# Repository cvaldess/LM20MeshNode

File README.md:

# LM20MeshNode

Pocket [Meshtastic](https://meshtastic.org/) node built around the Nordic **nRF54LM20A**
(Minew ME54BS13 module), with an Ebyte **E22-900MM22S** (SX1262) LoRa module, an Ebyte
**E108-GN04S** GNSS receiver and a Nordic **nPM1300** PMIC for a single-cell LiPo battery.
It connects to the phone over Bluetooth LE.

| Front | Back |
|-------|------|
|  |  |

> **Status:** revision 0.1, not yet manufactured or tested. A Meshtastic firmware variant is
> under review as a draft, not yet tested on hardware: see [Meshtastic firmware](#meshtastic-firmware).

## Features

- **MCU:** Minew ME54BS13 (nRF54LM20A, Bluetooth LE with integrated antenna), USB-C to the
  nRF54LM20A USB port, 2×5 1.27 mm Cortex Debug (SWD) header (J201) and debug UART pads.
- **LoRa:** Ebyte E22-900MM22S (SX1262, up to 22 dBm) with U.FL antenna connector (J301).
  TXEN is driven by DIO2 on the board; RXEN comes from the MCU.
- **GNSS:** Ebyte E108-GN04S with U.FL antenna connector (J401). Fit L401 (82 nH) to power an
  active antenna. The GNSS supply (nPM1300 BUCK1) is off at power-up and is switched by
  firmware; the backup supply (V_BCKP) stays on from 3.3 V.
- **Power:** nPM1300 PMIC with USB-C input and ESD protection, 1S LiPo charger (JST PH 2.0,
  J102), on-board 10 kΩ NTC, 3.3 V main rail (BUCK2), power button (SW101) on SHPHLD, charge
  and error LEDs, and a battery voltage divider to an ADC input.
- **User interface:** 0.91" 128×32 OLED (SSD1306) on the back, three side buttons (UP, OK,
  DOWN), magnetic buzzer and a status LED.
- **Sensors:** Nyfea SHT41-P-NF temperature/humidity sensor (SHT41 compatible), thermally
  isolated by a slot, and an ST LSM6DS3TR-C IMU wired for wake-on-motion (INT1 on P0.02).
- **Expansion:** 4-pin 1 mm I²C connector (J501, Qwiic-style pinout: GND, 3.3 V, SDA, SCL).
- **Board:** 4 layers (signal / GND / 3.3 V / signal), 40 × 85.68 mm, 1.6 mm, M2 mounting
  holes. All SMD parts are on the top side.

## nRF54LM20A pin map

| Function | Pin | Notes |
|----------|-----|-------|
| LoRa SPI (SPIM22): SCK, MOSI, MISO, NSS | P1.17, P1.16, P1.15, P1.18 | |
| LoRa BUSY, DIO1, NRST | P1.19, P1.23, P1.26 | |
| LoRa RXEN | P1.13 | TXEN from DIO2; optional MCU TXEN on P1.12 (R302, not fitted) |
| I²C (TWIM30): SDA, SCL | P0.03, P0.04 | 4.7 kΩ pull-ups |
| GNSS UART (UARTE20): MCU TX → GNSS RXD, GNSS TXD → MCU RX | P1.03, P1.29 | 1 kΩ series resistors |
| GNSS PPS, reset | P1.04, P1.00 | |
| GNSS power enable | P1.05 | To nPM1300 GPIO0 |
| PMIC interrupt | P1.06 | From nPM1300 GPIO1 |
| Battery voltage (divider 2 × 1 MΩ) | P1.30 (AIN2) | |
| Buttons UP, OK, DOWN | P1.27, P1.28, P1.25 | |
| Buzzer (PWM) | P1.09 | |
| Status LED | P2.00 | |
| IMU INT1, INT2 | P0.02, P0.05 | P0 can wake the chip from System OFF |
| Debug UART (UARTE00): TX, RX | P2.02, P2.07 | Test pads |

I²C devices: nPM1300 `0x6B`, LSM6DS3TR-C `0x6A`, SHT41 `0x44`, OLED `0x3C`.

### Firmware notes

- The nPM1300 starts with the **battery charger disabled**. Firmware must enable charging
  over I²C. The board is designed so that LoRa and Bluetooth work without a PMIC driver.
- The E22-900MM22S used here has a crystal, not a TCXO: do not define a DIO3 TCXO voltage.
- The GNSS rail (BUCK1) must be set to 3.3 V and enabled by firmware.

## Meshtastic firmware

The `lm20meshnode` variant is under review upstream. All three pull requests are open, and
nothing has run on hardware yet:

| Part | Pull request |
|------|--------------|
| Meshtastic variant (draft, on top of the nRF54LM20-DK support in [#12130](https://github.com/meshtastic/firmware/pull/12130)) | [meshtastic/firmware#12354](https://github.com/meshtastic/firmware/pull/12354) |
| Arduino core variant | [andyshinn/nRF54_Arduino#3](https://github.com/andyshinn/nRF54_Arduino/pull/3) |
| Bootloader board | [andyshinn/nRF54_Bootloader#3](https://github.com/andyshinn/nRF54_Bootloader/pull/3) |

Until they are merged, the variant builds from the `feat/lm20meshnode-variant` branch of
[cvaldess/firmware](https://github.com/cvaldess/firmware/tree/feat/lm20meshnode-variant) with
`pio run -e lm20meshnode`. The core and the bootloader come from forks (the core at a pinned commit,
the bootloader at the tag `v0.5.0-lm20meshnode.1`).

What the variant does on this board:

- **nPM1300**, set up over I²C at boot: BUCK1 (GNSS rail) at 3.3 V, switched by the PMIC's GPIO0,
  which the GPS code drives from P1.05; battery charger on at 200 mA (`NPM1300_CHARGE_CURRENT_MA`),
  4.20 V (4.00 V in the warm region), with the on-board 10 kΩ NTC; USB input limit 500 mA. BUCK2,
  the 3.3 V main rail, is left on its VSET2 setting. After USB is unplugged and plugged in again,
  the PMIC goes back to its 100 mA startup input limit until the next boot.
- **LoRa** with RXEN from the MCU and TXEN from DIO2, no TCXO. **GNSS** on `Serial1` at 38400 bps.
- **Buttons:** UP, DOWN and OK navigate the screen (up/down input driver). **OLED** at 128×32,
  **buzzer**, **status LED**, **battery** level from AIN2, and the SHT41 and LSM6DS3TR-C drivers.
- **USB-C:** console and Meshtastic API over USB CDC; firmware updates over USB (serial DFU or a
  UF2 drive) or over Bluetooth.
- **Bootloader** (64 KB, application at `0x10000`): hold **OK** at reset for USB DFU (UF2 drive
  `LM20MN-BOOT`), **OK + DOWN** for Bluetooth OTA. The status LED shows the bootloader state.

Not tested yet, besides the board itself: the nPM1300 setup, GPS on the nRF54 platform (no other
nRF54 variant uses it so far), the 128×32 screen layout and the battery reading through the
2 × 1 MΩ divider.

## Manufacturing

The [`fab/pcbway/`](fab/pcbway/) folder contains:

- `nrflm20-meshnode_rev0.1_pcbway.zip`: Gerber files (4 copper layers, masks, top paste,
  silkscreen, outline), Excellon drill files (PTH and NPTH) and an IPC-D-356 netlist.
- `gerber/`: the same files unzipped, plus drill maps and the drill report.
- `nrflm20-meshnode-BOM-PCBWay.csv`: bill of materials (40 lines, 71 parts) with manufacturer part
  numbers and LCSC codes. A few passives are generic parts, listed by specification.
- `nrflm20-meshnode-CPL-PCBWay.csv`: component placement (centroid) file in millimetres, in the
  same coordinate system as the Gerber files. The OLED (DS501) is the only part on the bottom side.
- `pedido_pcbway.txt`: order settings and pre-production checks (in Spanish).

Not fitted (DNP) and left out of the BOM and placement files: R302, R404, C303, C304. Mounting
holes and test points are not parts and are left out too.

Board: 4 layers, 1.6 mm, 1 oz copper, ENIG recommended, minimum track/space 0.2 mm, minimum
drill 0.3 mm. Stencil: top side only, 0.10 mm. The standard PCBWay 4-layer stackup is fine;
impedance control is not needed.

The files are generated from the saved board with `docs/gen/fab_pcbway.py` (Gerber, drill,
IPC-D-356) and `docs/gen/bom_cpl_pcbway.py` (BOM and placement), using KiCad's Python.

## Design files

- [KiCad 10](https://www.kicad.org/) project: `nrflm20-meshnode.kicad_pro`. The root schematic
  has five sheets: power, MCU, LoRa, GNSS and interface.
- `libs/`: project symbols, footprints and 3D models. The ME54BS13 and E108-GN04S 3D models
  were drawn from their datasheets (generators in `docs/gen/`).
- `docs/`: block diagram and schematic drafts (SVG). `docs/gen/` has the Python scripts used
  during the design.
- `lista_compra.txt`: shopping list (in Spanish).

Some footprints and 3D models come from [easyeda2kicad](https://github.com/uPesy/easyeda2kicad.py)
(`${EASYEDA2KICAD}`). The footprints are stored in the board file, but their 3D models are
not included in this repository.

## Credits

- **Designed by:** solutions@cvaldess.com
- **Made with:** [Claude Code](https://claude.com/claude-code), [KiCad](https://www.kicad.org/)
  and [Konnect-EDA](https://github.com/Orchis-ai-LLC/Konnect-EDA)
- **Sponsor:** [PCBWay](https://www.pcbway.com/)

## License

Copyright © 2026 CValdesS.

This source describes Open Hardware and is licensed under the CERN-OHL-S v2
([LICENSE](LICENSE)). You may redistribute and modify this source and make products using it
under the terms of the CERN-OHL-S v2. This source is distributed WITHOUT ANY EXPRESS OR IMPLIED
WARRANTY, INCLUDING OF MERCHANTABILITY, SATISFACTORY QUALITY AND FITNESS FOR A PARTICULAR
PURPOSE. Please see the CERN-OHL-S v2 for applicable conditions.

Source location: https://github.com/cvaldess/LM20MeshNode

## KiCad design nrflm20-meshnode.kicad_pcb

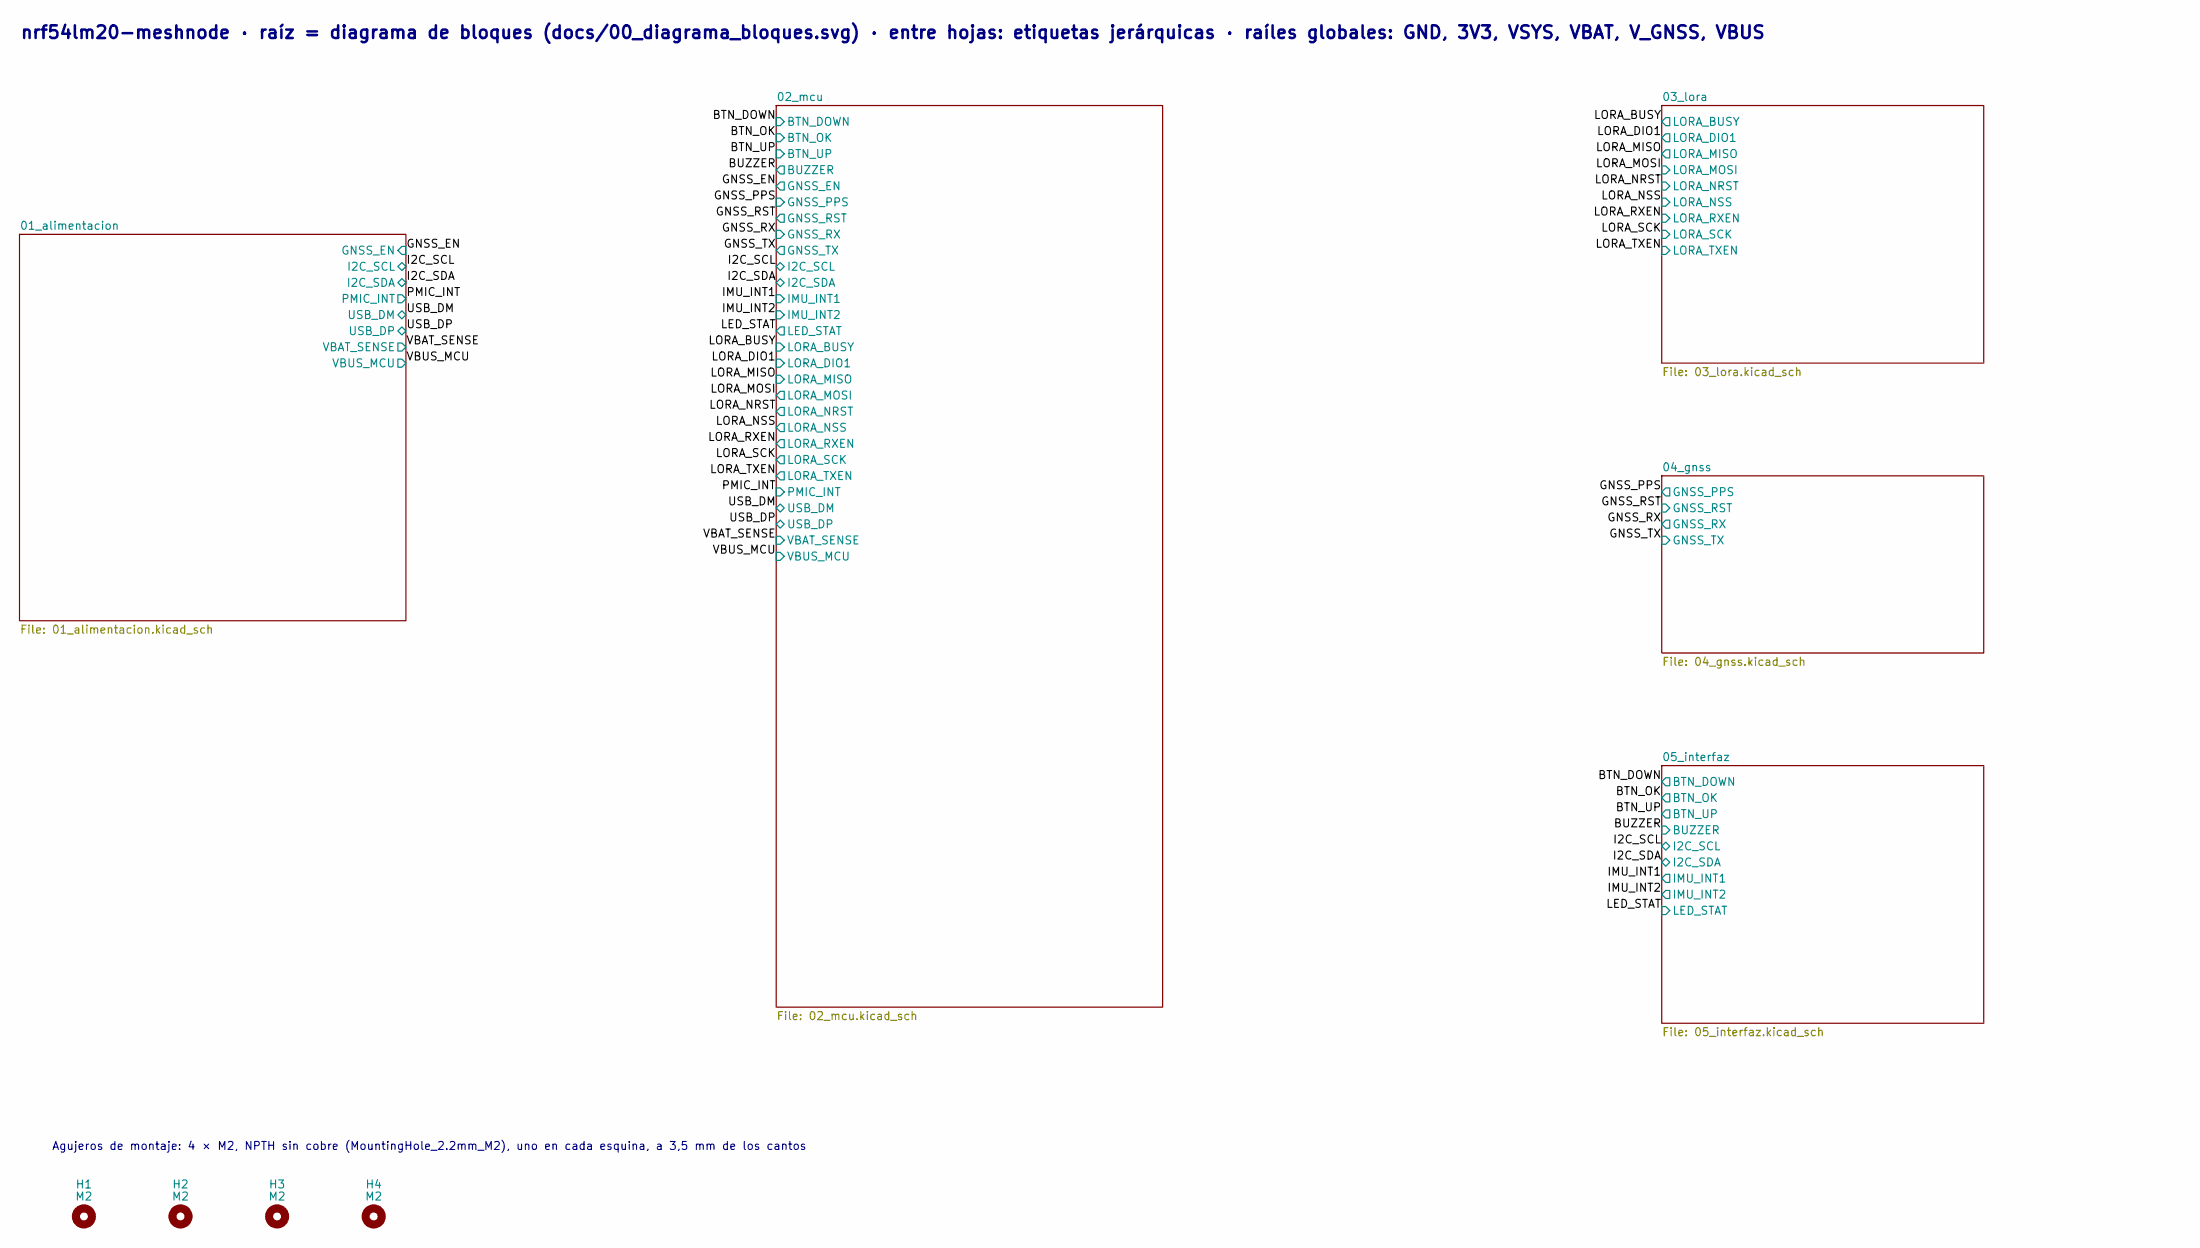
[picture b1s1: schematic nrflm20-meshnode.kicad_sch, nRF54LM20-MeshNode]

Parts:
H1, H2, H3, H4: M2; MountingHole_2.2mm_M2

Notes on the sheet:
nrf54lm20-meshnode · raíz = diagrama de bloques (docs/00_diagrama_bloques.svg) · entre hojas: etiquetas jerárquicas · raíles globales: GND, 3V3, VSYS, VBAT, V_GNSS, VBUS
Agujeros de montaje: 4 × M2, NPTH sin cobre (MountingHole_2.2mm_M2), uno en cada esquina, a 3,5 mm de los cantos

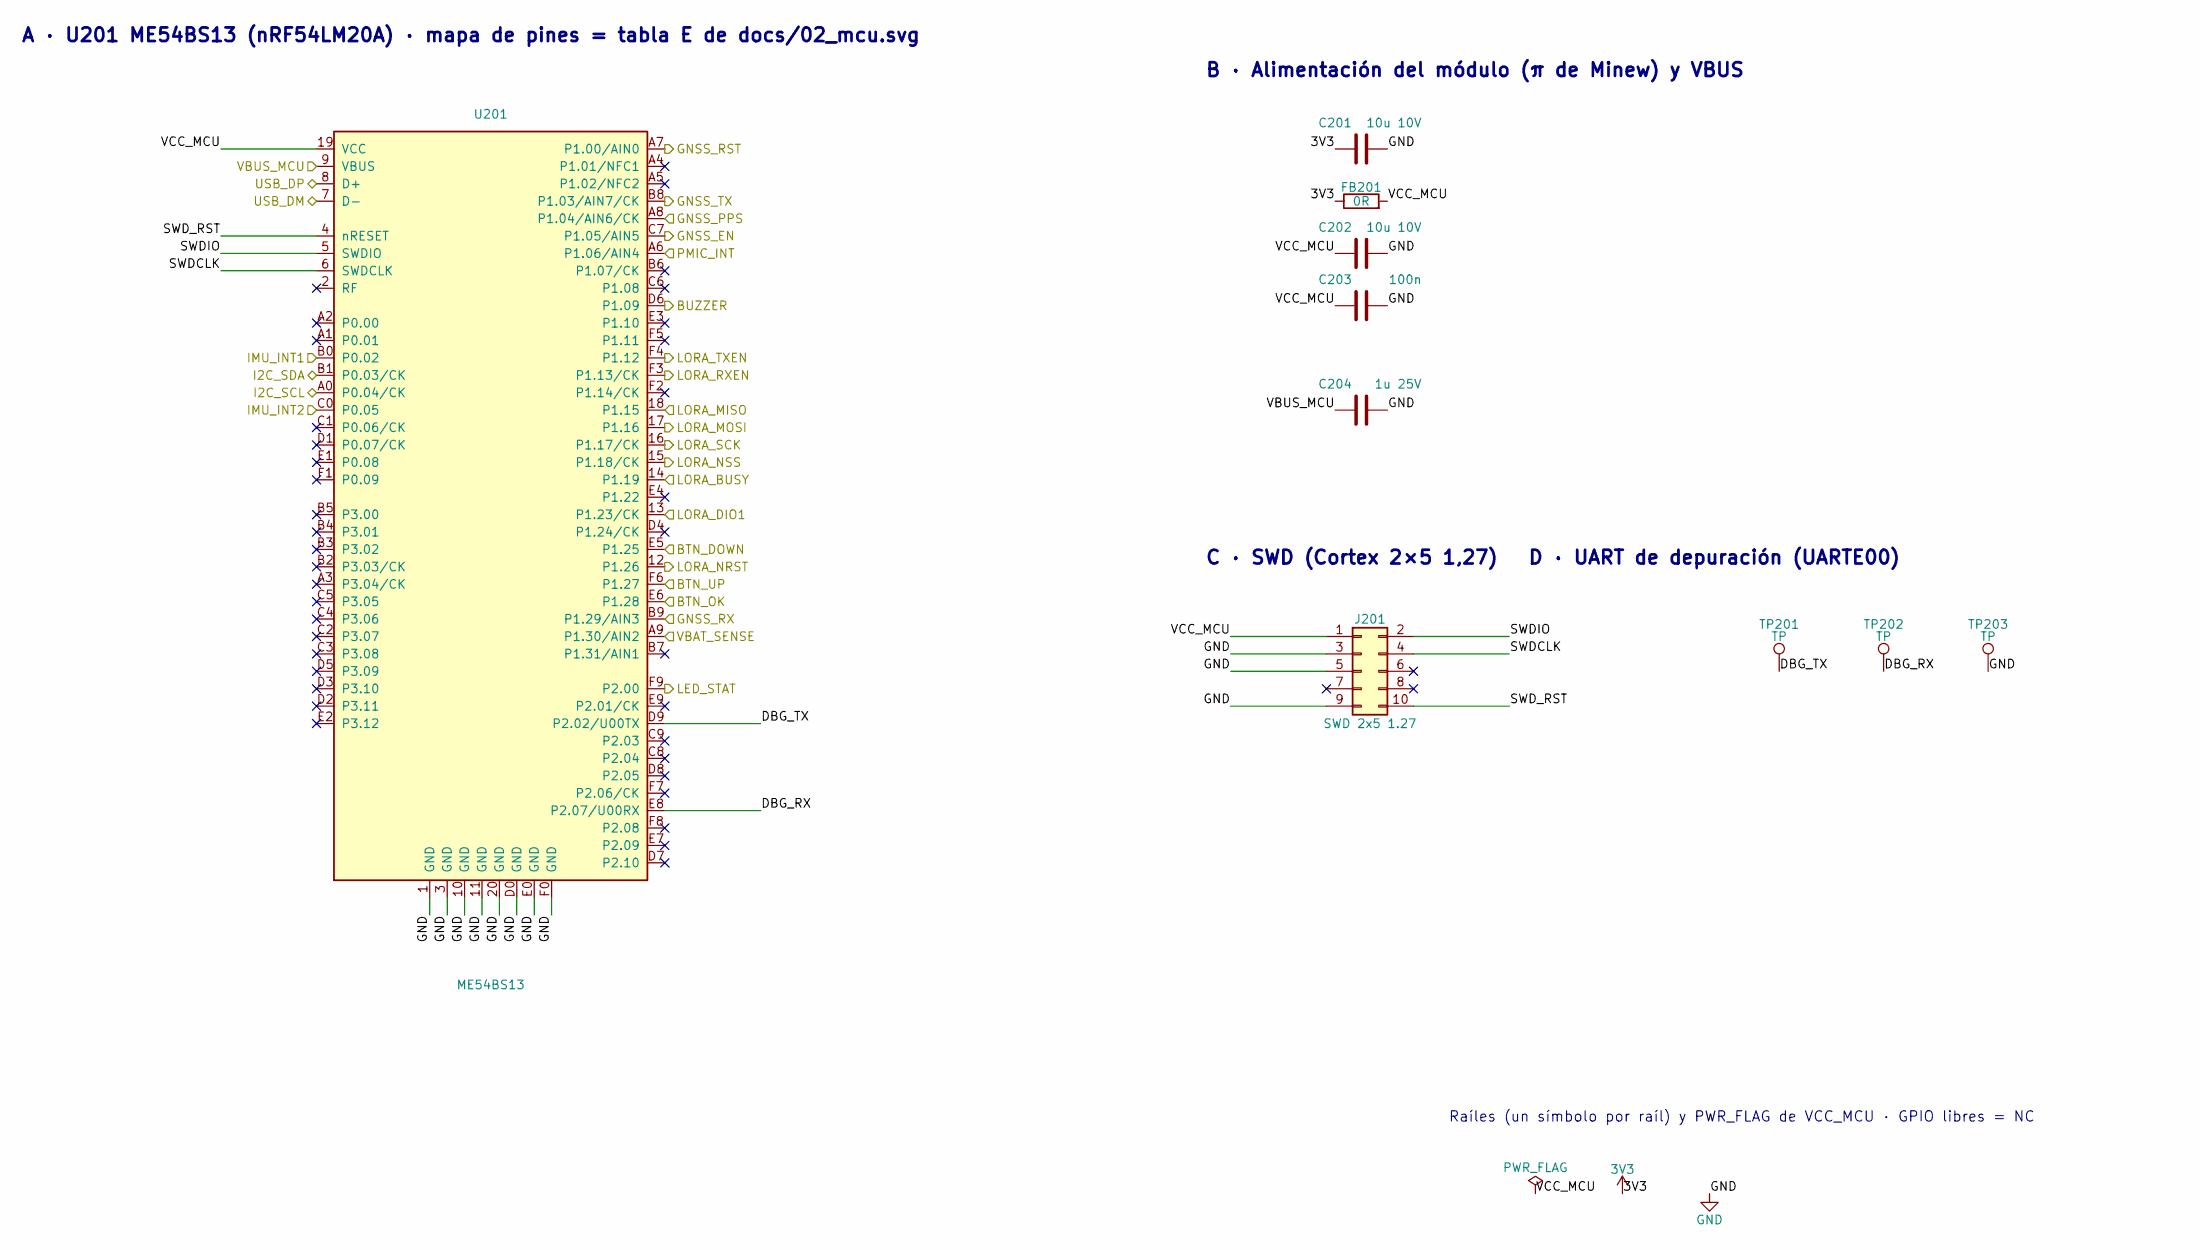
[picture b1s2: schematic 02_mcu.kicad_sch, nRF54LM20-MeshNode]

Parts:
C201, C202: 10u 10V; C_0603_1608Metric
C203: 100n; C_0402_1005Metric; MPN CL05B104KO5NNNC; LCSC Part C1525
C204: 1u 25V; C_0402_1005Metric; MPN CL05A105KA5NQNC; LCSC Part C52923
FB201: 0R; R_0603_1608Metric
J201: SWD 2x5 1.27; PinHeader_2x05_P1.27mm_Vertical_SMD; MPN HX PZ1.27-2x5P TP; LCSC Part C41376037
TP201, TP202, TP203: TP; TestPoint_Pad_D1.0mm
U201: ME54BS13; MPN ME54BS13 (nRF54LM20A)

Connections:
3V3: C201.1, FB201.1; also elsewhere on the board
/02_mcu/DBG_RX: TP202.1 (1_1), U201.E8 (P2.07/U00RX)
/02_mcu/DBG_TX: TP201.1 (1_1), U201.D9 (P2.02/U00TX)
/02_mcu/SWDCLK: J201.4, U201.6 (SWDCLK)
/02_mcu/SWDIO: J201.2, U201.5 (SWDIO)
/02_mcu/SWD_RST: J201.10, U201.4 (nRESET)
/02_mcu/VCC_MCU: C202.1, C203.1, FB201.2, J201.1, U201.19 (VCC)
/BTN_DOWN: U201.E5 (P1.25); also elsewhere on the board
/BTN_OK: U201.E6 (P1.28); also elsewhere on the board
/BTN_UP: U201.F6 (P1.27); also elsewhere on the board
/BUZZER: U201.D6 (P1.09); also elsewhere on the board
/GNSS_EN: U201.C7 (P1.05/AIN5); also elsewhere on the board
/GNSS_PPS: U201.A8 (P1.04/AIN6/CK); also elsewhere on the board
/GNSS_RST: U201.A7 (P1.00/AIN0); also elsewhere on the board
/GNSS_RX: U201.B9 (P1.29/AIN3); also elsewhere on the board
/GNSS_TX: U201.B8 (P1.03/AIN7/CK); also elsewhere on the board
/I2C_SCL: U201.A0 (P0.04/CK); also elsewhere on the board
/I2C_SDA: U201.B1 (P0.03/CK); also elsewhere on the board
/IMU_INT1: U201.B0 (P0.02); also elsewhere on the board
/IMU_INT2: U201.C0 (P0.05); also elsewhere on the board
/LED_STAT: U201.F9 (P2.00); also elsewhere on the board
/LORA_BUSY: U201.14 (P1.19); also elsewhere on the board
/LORA_DIO1: U201.13 (P1.23/CK); also elsewhere on the board
/LORA_MISO: U201.18 (P1.15); also elsewhere on the board
/LORA_MOSI: U201.17 (P1.16); also elsewhere on the board
/LORA_NRST: U201.12 (P1.26); also elsewhere on the board
/LORA_NSS: U201.15 (P1.18/CK); also elsewhere on the board
/LORA_RXEN: U201.F3 (P1.13/CK); also elsewhere on the board
/LORA_SCK: U201.16 (P1.17/CK); also elsewhere on the board
/LORA_TXEN: U201.F4 (P1.12); also elsewhere on the board
/PMIC_INT: U201.A6 (P1.06/AIN4); also elsewhere on the board
/USB_DM: U201.7 (D-); also elsewhere on the board
/USB_DP: U201.8 (D+); also elsewhere on the board
/VBAT_SENSE: U201.A9 (P1.30/AIN2); also elsewhere on the board
/VBUS_MCU: C204.1, U201.9 (VBUS); also elsewhere on the board
GND: C201.2, C202.2, C203.2, C204.2, J201.3, J201.5, J201.9, TP203.1 (1_1), U201.1 (GND), U201.3 (GND), U201.10 (GND), U201.11 (GND), U201.20 (GND), U201.D0 (GND), U201.E0 (GND), U201.F0 (GND); also elsewhere on the board

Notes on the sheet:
B · Alimentación del módulo (π de Minew) y VBUS
A · U201 ME54BS13 (nRF54LM20A) · mapa de pines = tabla E de docs/02_mcu.svg
C · SWD (Cortex 2×5 1,27) D · UART de depuración (UARTE00)
Raíles (un símbolo por raíl) y PWR_FLAG de VCC_MCU · GPIO libres = NC

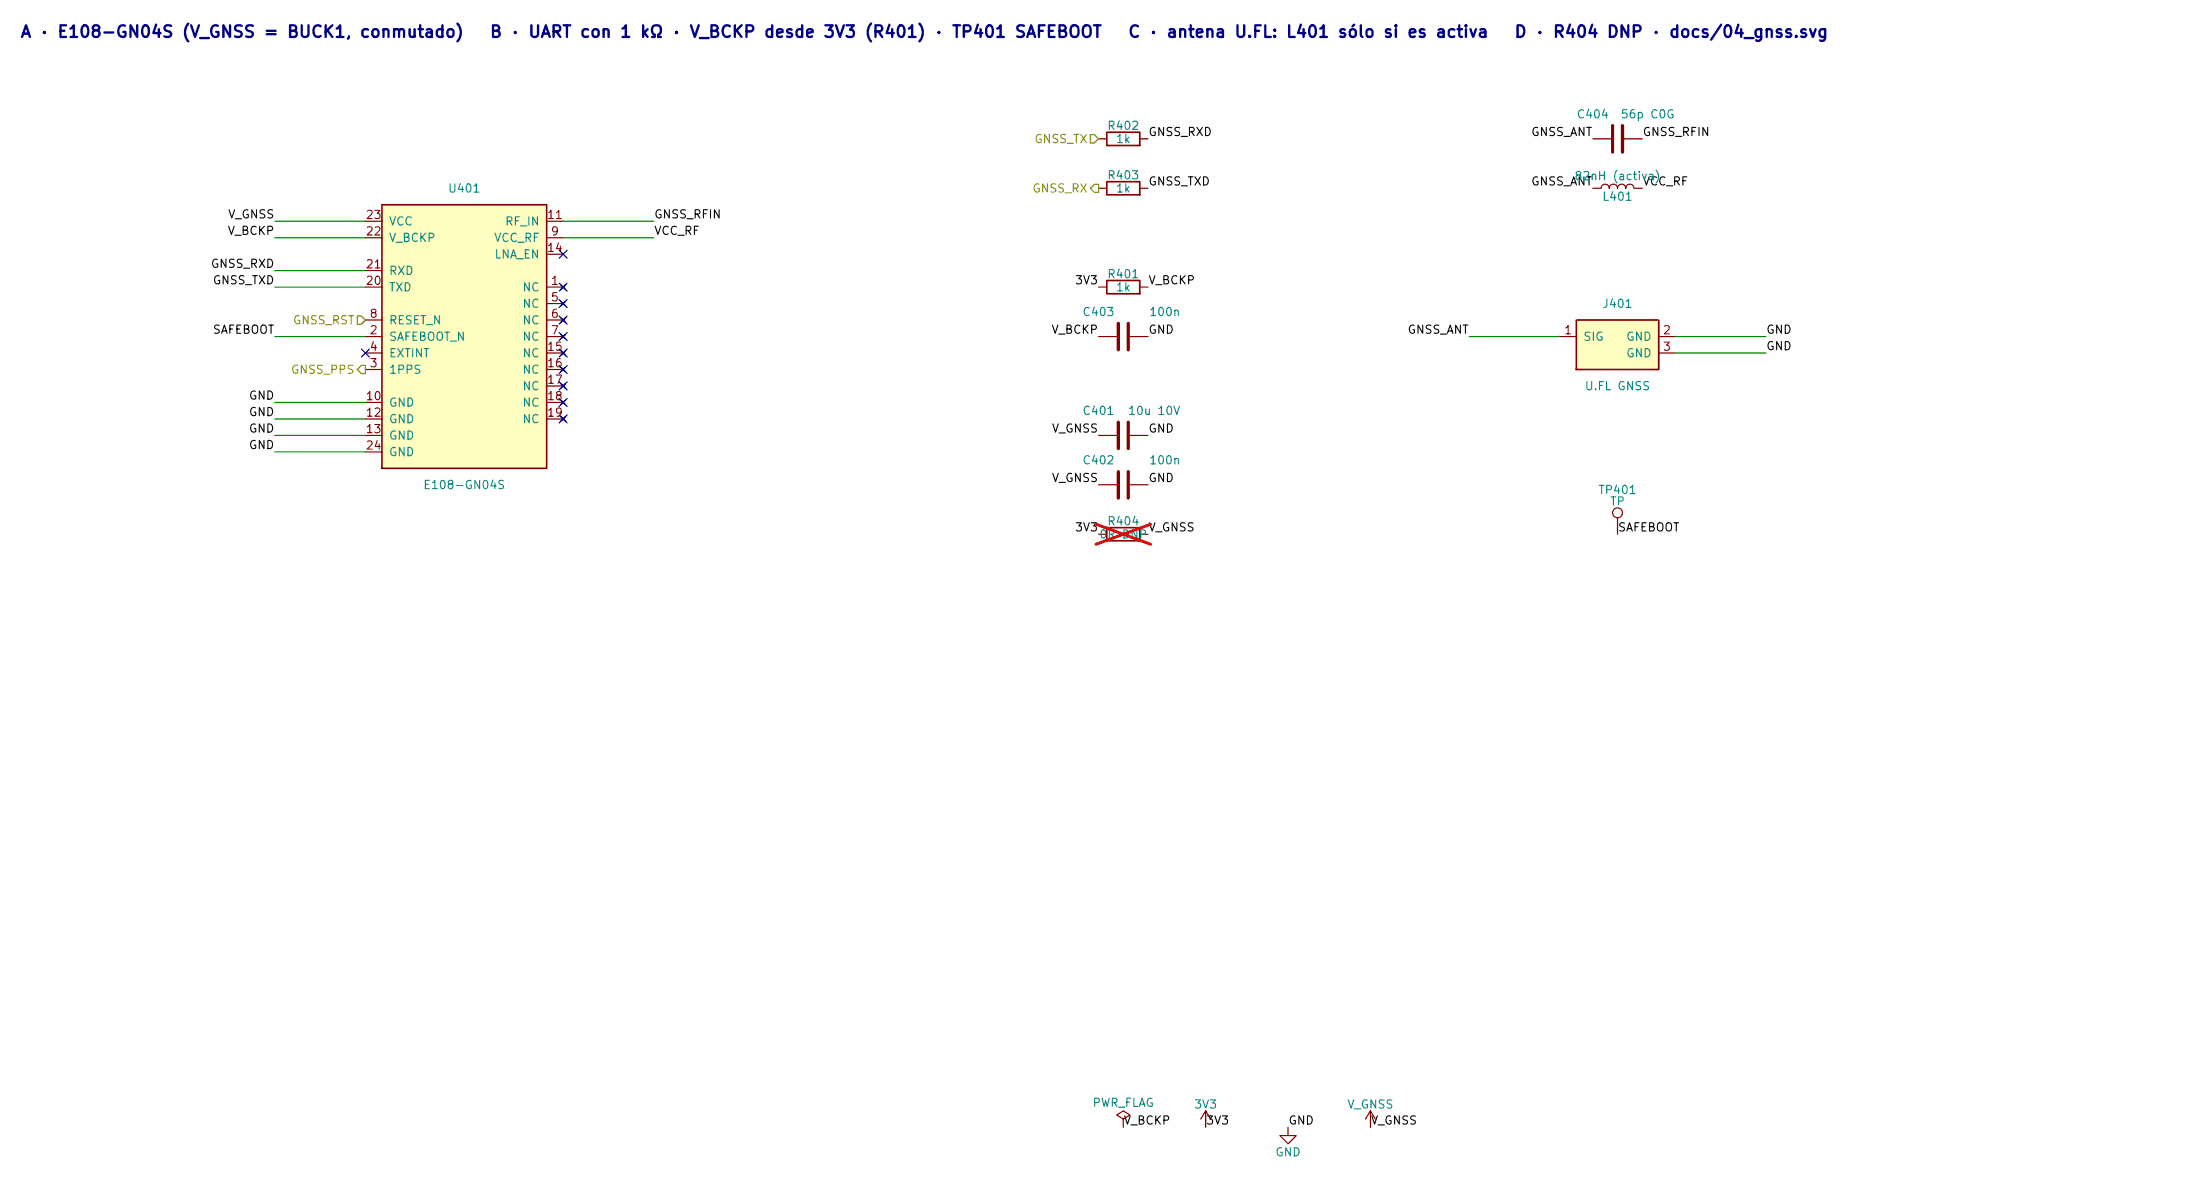
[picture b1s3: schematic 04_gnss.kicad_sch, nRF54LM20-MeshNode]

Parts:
C401: 10u 10V; C_0603_1608Metric
C402, C403: 100n; C_0402_1005Metric; MPN CL05B104KO5NNNC; LCSC Part C1525
C404: 56p C0G; C_0402_1005Metric; MPN CL05C560JB5NNNC; LCSC Part C84707
J401: U.FL GNSS; IPEX-SMD_BWIPX-1-001E; MPN BWU.FL-IPEX1; LCSC Part C5137195
L401: 82nH (activa); L_0402_1005Metric; MPN LQG15HS82NJ02D; LCSC Part C98002
R401, R402, R403: 1k; R_0402_1005Metric; MPN 0402WGF1001TCE; LCSC Part C11702
R404: 0R DNP; R_0402_1005Metric; MPN RC0402FR-070RL; LCSC Part C106231; not fitted
TP401: TP; TestPoint_Pad_D1.0mm
U401: E108-GN04S; MPN E108-GN04S

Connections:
3V3: R401.1, R404.1; also elsewhere on the board
/04_gnss/GNSS_ANT: C404.1, J401.1 (SIG), L401.1
/04_gnss/GNSS_RFIN: C404.2, U401.11 (RF_IN)
/04_gnss/GNSS_RXD: R402.2, U401.21 (RXD)
/04_gnss/GNSS_TXD: R403.2, U401.20 (TXD)
/04_gnss/SAFEBOOT: TP401.1 (1_1), U401.2 (SAFEBOOT_N)
/04_gnss/VCC_RF: L401.2, U401.9 (VCC_RF)
/04_gnss/V_BCKP: C403.1, R401.2, U401.22 (V_BCKP)
/GNSS_PPS: U401.3 (1PPS); also elsewhere on the board
/GNSS_RST: U401.8 (RESET_N); also elsewhere on the board
/GNSS_RX: R403.1; also elsewhere on the board
/GNSS_TX: R402.1; also elsewhere on the board
GND: C401.2, C402.2, C403.2, J401.2 (GND), J401.3 (GND), U401.10 (GND), U401.12 (GND), U401.13 (GND), U401.24 (GND); also elsewhere on the board
V_GNSS: C401.1, C402.1, R404.2, U401.23 (VCC); also elsewhere on the board

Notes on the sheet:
A · E108-GN04S (V_GNSS = BUCK1, conmutado) B · UART con 1 kΩ · V_BCKP desde 3V3 (R401) · TP401 SAFEBOOT C · antena U.FL: L401 sólo si es activa D · R404 DNP · docs/04_gnss.svg

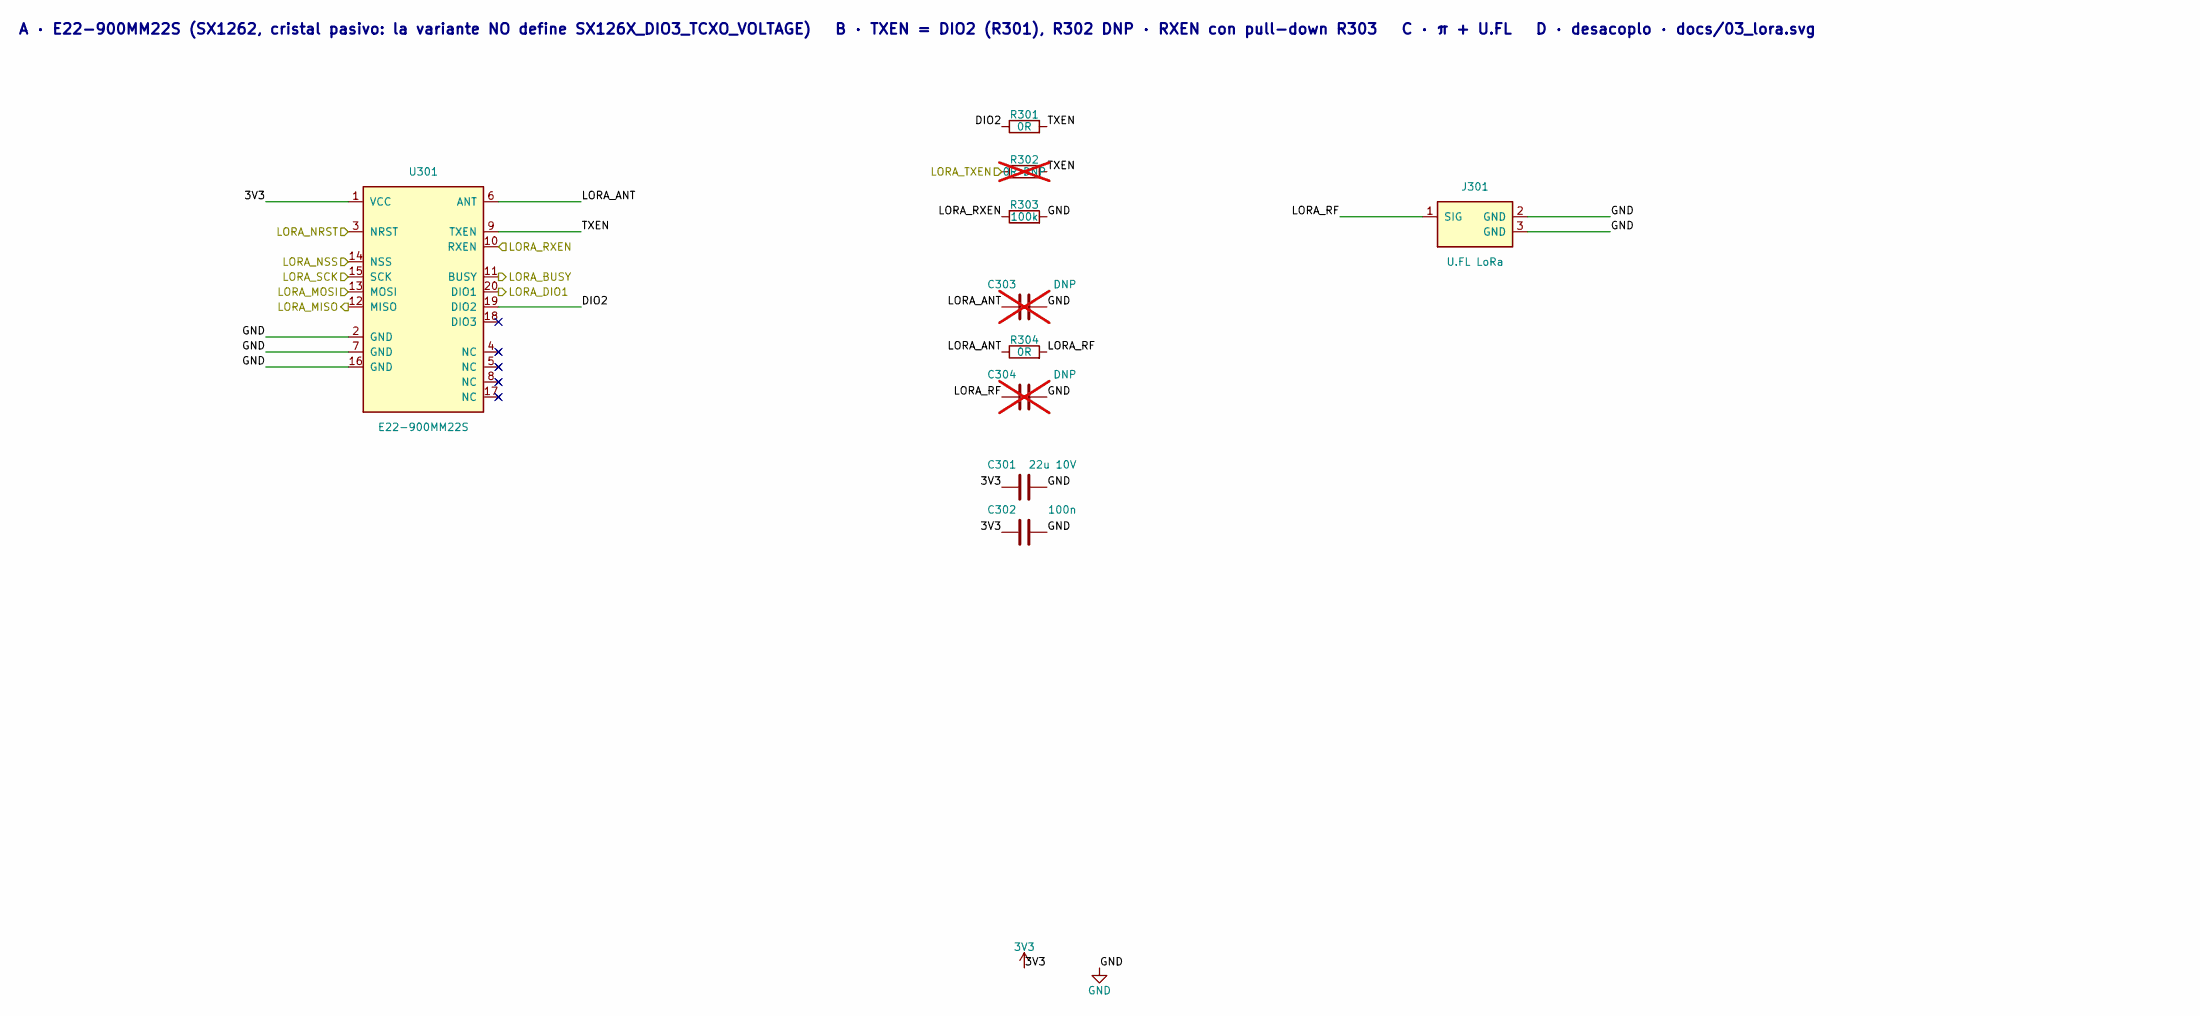
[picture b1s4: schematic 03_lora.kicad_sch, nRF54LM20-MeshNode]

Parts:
C301: 22u 10V; C_0603_1608Metric
C302: 100n; C_0402_1005Metric; MPN CL05B104KO5NNNC; LCSC Part C1525
C303, C304: DNP; C_0402_1005Metric; not fitted
J301: U.FL LoRa; IPEX-SMD_BWIPX-1-001E; MPN BWU.FL-IPEX1; LCSC Part C5137195
R301, R304: 0R; R_0402_1005Metric; MPN RC0402FR-070RL; LCSC Part C106231
R302: 0R DNP; R_0402_1005Metric; MPN RC0402FR-070RL; LCSC Part C106231; not fitted
R303: 100k; R_0402_1005Metric; MPN RC0402FR-07100KL; LCSC Part C60491
U301: E22-900MM22S; E22-xxxMM22S; MPN E22-900MM22S

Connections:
3V3: C301.1, C302.1, U301.1 (VCC); also elsewhere on the board
/03_lora/DIO2: R301.1, U301.19 (DIO2)
/03_lora/LORA_ANT: C303.1, R304.1, U301.6 (ANT)
/03_lora/LORA_RF: C304.1, J301.1 (SIG), R304.2
/03_lora/TXEN: R301.2, R302.2, U301.9 (TXEN)
/LORA_BUSY: U301.11 (BUSY); also elsewhere on the board
/LORA_DIO1: U301.20 (DIO1); also elsewhere on the board
/LORA_MISO: U301.12 (MISO); also elsewhere on the board
/LORA_MOSI: U301.13 (MOSI); also elsewhere on the board
/LORA_NRST: U301.3 (NRST); also elsewhere on the board
/LORA_NSS: U301.14 (NSS); also elsewhere on the board
/LORA_RXEN: R303.1, U301.10 (RXEN); also elsewhere on the board
/LORA_SCK: U301.15 (SCK); also elsewhere on the board
/LORA_TXEN: R302.1; also elsewhere on the board
GND: C301.2, C302.2, C303.2, C304.2, J301.2 (GND), J301.3 (GND), R303.2, U301.2 (GND), U301.7 (GND), U301.16 (GND); also elsewhere on the board

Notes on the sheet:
A · E22-900MM22S (SX1262, cristal pasivo: la variante NO define SX126X_DIO3_TCXO_VOLTAGE) B · TXEN = DIO2 (R301), R302 DNP · RXEN con pull-down R303 C · π + U.FL D · desacoplo · docs/03_lora.svg

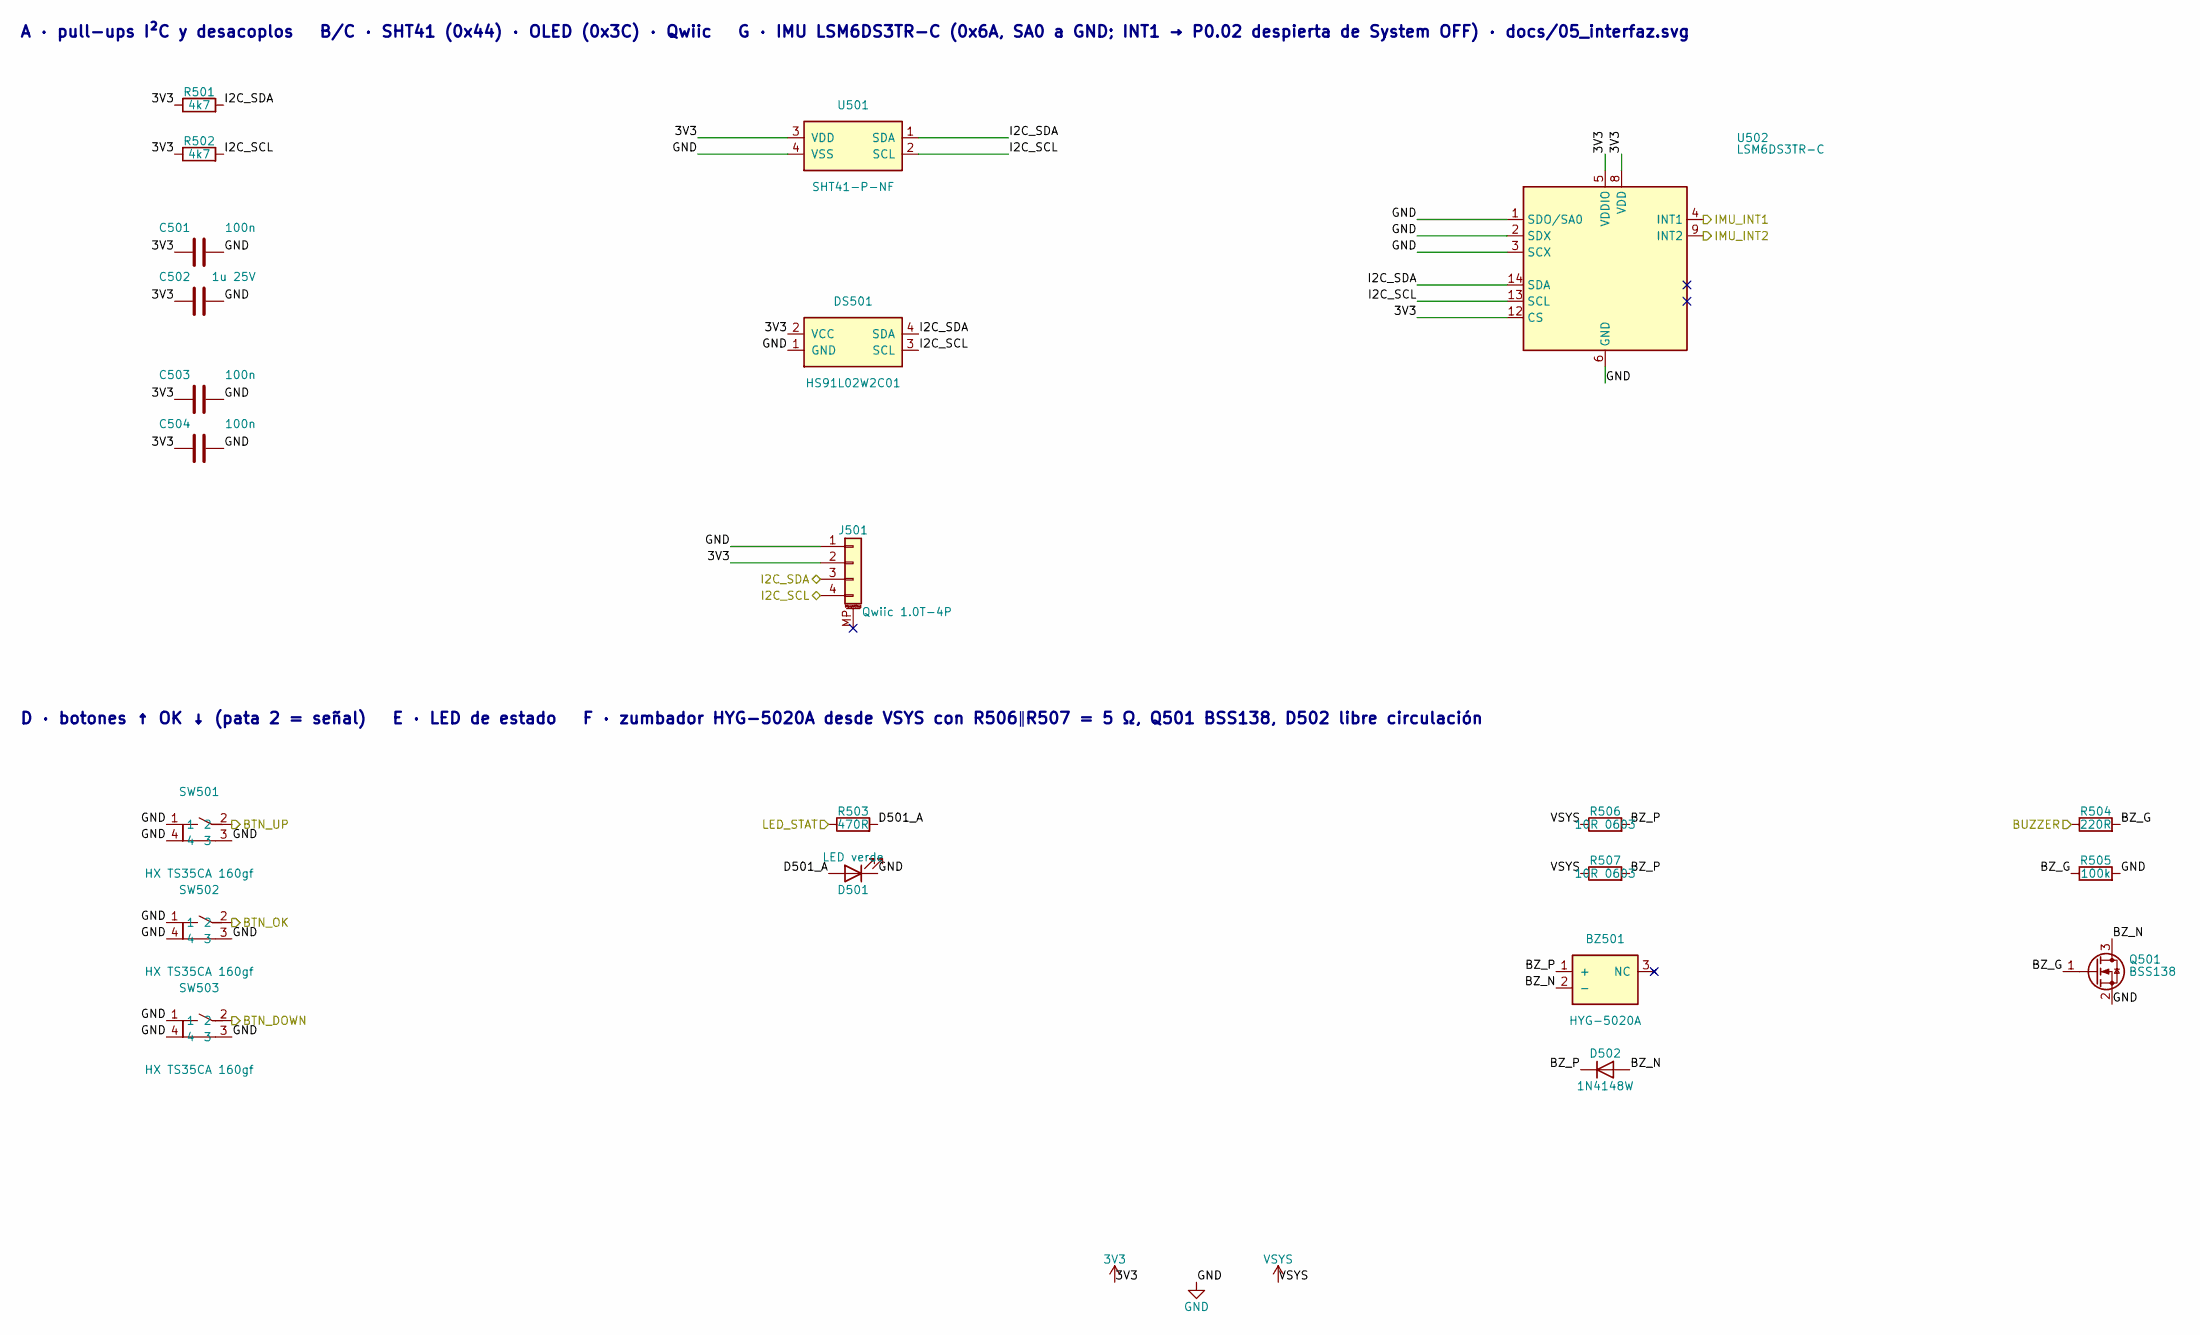
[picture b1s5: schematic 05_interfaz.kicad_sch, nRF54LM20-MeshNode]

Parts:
BZ501: HYG-5020A; BUZ-SMD_3P-L5.0-W5.0-P3.50-BL; MPN HYG-5020A; LCSC Part C7544810
C501, C503, C504: 100n; C_0402_1005Metric; MPN CL05B104KO5NNNC; LCSC Part C1525
C502: 1u 25V; C_0402_1005Metric; MPN CL05A105KA5NQNC; LCSC Part C52923
D501: LED verde; LED_0603_1608Metric; MPN XL-1608UGC-06A; LCSC Part C7371903
D502: 1N4148W; D_SOD-123; MPN 1N4148W; LCSC Part C917030
DS501: HS91L02W2C01; OLED-TH_L38.0-W12.0_HS91L02W2C01; MPN HS91L02W2C01; LCSC Part C5248081
J501: Qwiic 1.0T-4P; BOOMELE_1.0T-4P_1x04-1MP_P1.00mm_Horizontal; MPN 1.0T-4P; LCSC Part C970137
Q501: BSS138; SOT-23; MPN BSS138; LCSC Part C27140738
R501, R502: 4k7; R_0402_1005Metric; MPN RC0402FR-074K7L; LCSC Part C105871
R503: 470R; R_0402_1005Metric; MPN 0402WGF4700TCE; LCSC Part C25117
R504: 220R; R_0402_1005Metric; MPN 0402WGF2200TCE; LCSC Part C25091
R505: 100k; R_0402_1005Metric; MPN RC0402FR-07100KL; LCSC Part C60491
R506, R507: 10R 0603; R_0603_1608Metric
SW501, SW502, SW503: HX TS35CA 160gf; KEY-SMD_HX-TS35CA-250GF; MPN HX TS35CA 160gf; LCSC Part C25168837
U501: SHT41-P-NF; DFN-4_L1.5-W1.5-SHT41-AD1B-R2; MPN SHT41-P-NF; LCSC Part C55108905
U502: LSM6DS3TR-C; LGA-14_L3.0-W2.5-P0.50-TL; MPN LSM6DS3TR-C; LCSC Part C967633

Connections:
3V3: C501.1, C502.1, C503.1, C504.1, DS501.2 (VCC), J501.2, R501.1, R502.1, U501.3 (VDD), U502.5 (VDDIO), U502.8 (VDD), U502.12 (CS); also elsewhere on the board
/05_interfaz/BZ_G: Q501.1 (G), R504.2, R505.1
/05_interfaz/BZ_N: BZ501.2 (-), D502.2 (A), Q501.3 (D)
/05_interfaz/BZ_P: BZ501.1 (+), D502.1 (K), R506.2, R507.2
/05_interfaz/D501_A: D501.2 (A), R503.2
/BTN_DOWN: SW503.2; also elsewhere on the board
/BTN_OK: SW502.2; also elsewhere on the board
/BTN_UP: SW501.2; also elsewhere on the board
/BUZZER: R504.1; also elsewhere on the board
/I2C_SCL: DS501.3 (SCL), J501.4, R502.2, U501.2 (SCL), U502.13 (SCL); also elsewhere on the board
/I2C_SDA: DS501.4 (SDA), J501.3, R501.2, U501.1 (SDA), U502.14 (SDA); also elsewhere on the board
/IMU_INT1: U502.4 (INT1); also elsewhere on the board
/IMU_INT2: U502.9 (INT2); also elsewhere on the board
/LED_STAT: R503.1; also elsewhere on the board
GND: C501.2, C502.2, C503.2, C504.2, D501.1 (K), DS501.1 (GND), J501.1, Q501.2 (S), R505.2, SW501.1, SW501.3, SW501.4, SW502.1, SW502.3, SW502.4, SW503.1, SW503.3, SW503.4, U501.4 (VSS), U502.1 (SDO/SA0), U502.2 (SDX), U502.3 (SCX), U502.6 (GND), U502.7 (GND); also elsewhere on the board
VSYS: R506.1, R507.1; also elsewhere on the board

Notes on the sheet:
A · pull-ups I²C y desacoplos B/C · SHT41 (0x44) · OLED (0x3C) · Qwiic G · IMU LSM6DS3TR-C (0x6A, SA0 a GND; INT1 → P0.02 despierta de System OFF) · docs/05_interfaz.svg
D · botones ↑ OK ↓ (pata 2 = señal) E · LED de estado F · zumbador HYG-5020A desde VSYS con R506∥R507 = 5 Ω, Q501 BSS138, D502 libre circulación
